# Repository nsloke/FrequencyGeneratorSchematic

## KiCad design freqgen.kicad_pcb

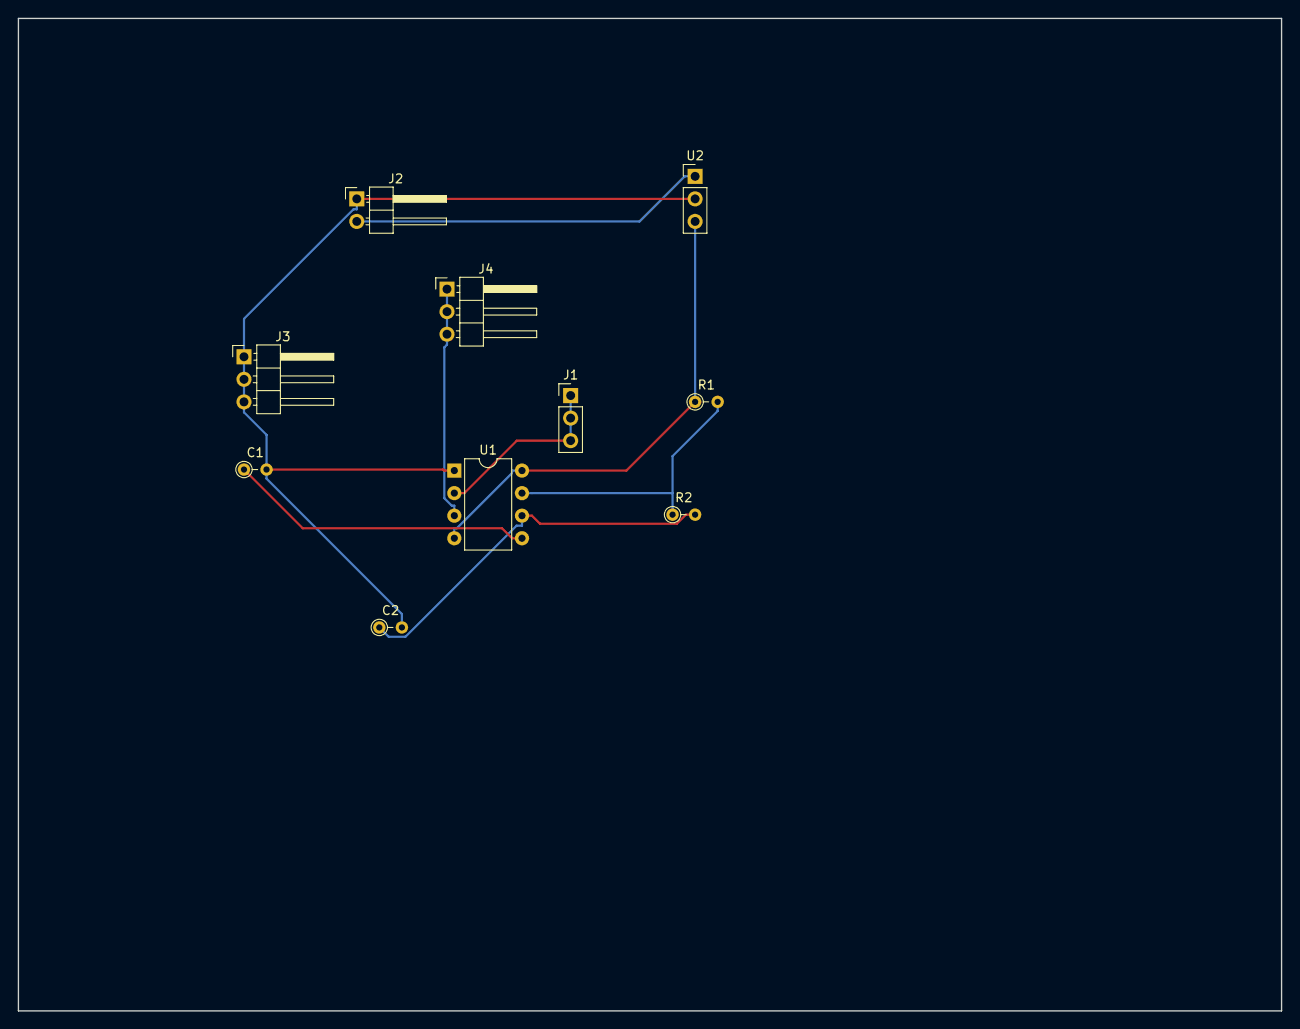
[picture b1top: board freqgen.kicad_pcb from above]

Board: 2 copper layers, 142.2 x 111.8 mm, 10 parts (0 on the bottom side), 8 nets.

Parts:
C1: 0.01uF; R_Axial_DIN0204_L3.6mm_D1.6mm_P2.54mm_Vertical
C2: 100pF; R_Axial_DIN0204_L3.6mm_D1.6mm_P2.54mm_Vertical
J1: Input Trigger Raspi; PinHeader_1x03_P2.54mm_Vertical
J2: Battery Input Terminal(1GND,2VCC); PinHeader_1x02_P2.54mm_Horizontal
J3: GND Matching; PinHeader_1x03_P2.54mm_Horizontal
J4: Output Frequency; PinHeader_1x03_P2.54mm_Horizontal
R1: 220K; R_Axial_DIN0204_L3.6mm_D1.6mm_P2.54mm_Vertical
R2: 1K; R_Axial_DIN0204_L3.6mm_D1.6mm_P2.54mm_Vertical
U1: NE555; DIP-8_W7.62mm
U2: L7805; PinHeader_1x03_P2.54mm_Vertical

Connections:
unnamed: C1.1, U1.5
unnamed: C1.2, C2.2, J2.1, J3.1, J3.2, J3.3, U1.1, U2.2
unnamed: C2.1, R2.2, U1.6
unnamed: J1.1, J1.2, J1.3, U1.2
unnamed: J2.2, U2.1
unnamed: J4.1, J4.2, J4.3, U1.3
unnamed: R1.1, U1.4, U1.8, U2.3
unnamed: R1.2, R2.1, U1.7

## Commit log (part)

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2020-08-04 Final Schematic
